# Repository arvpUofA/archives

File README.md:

# ARCHIVES

Last updated: 26th Aug 2016

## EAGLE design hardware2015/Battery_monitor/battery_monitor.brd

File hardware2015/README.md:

# Hardware for Aqua Ursa (2015)

* 2 x Battery Display (Battery_monitor/battery_display) [ Dim: 01.1 x 3.95 in ]
* 4 x Battery Monitor (Battery_monitor/battery_monitor) [ Dim: 0.73 x 1.59 in ]
* 2 x Display (Display/display) [ Dim: 2.72 x 3.79 in ]
* 2 x Motor (Motor/Motor_board) [ Dim: 4.65 x 3.66 in ]
* 2 x Sensor (Sensor/sensors) [ Dim: 1.51 x 1.25 in ]
* 2 x Sonar (Sonar/Sonar) [ Dim: 3.91 x 3.15 in ]

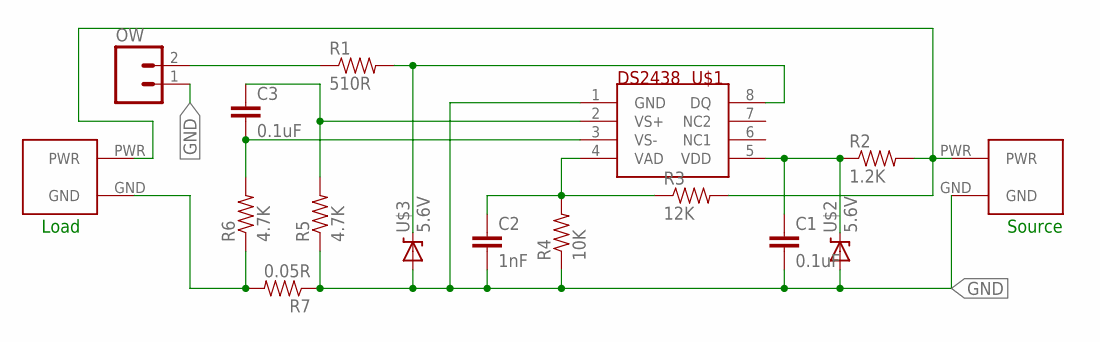
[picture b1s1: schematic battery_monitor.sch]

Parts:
C1, C3: 0.1uF; 0805
C2: 1nF; 0805
LOAD: AND_PWR
OW: M02POLAR_LOCK; MOLEX-1X2_LOCK
R1: 510R; 0805
R2: 1.2K; 0805
R3: 12K; 0805
R4: 10K; 0805
R5, R6: 4.7K; 0805
R7: 0.05R; 1206
SOURCE: AND_PWR
U$1: DS2438Z; SOIC8
U$2, U$3: 5.6V; SMB-DIODE

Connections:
GND: C1.2, C2.2, OW.1, R4.1, R5.1, R7.1, SOURCE.GND, U$1.1 (GND), U$2.A, U$3.A
unnamed: C1.1, R2.1, U$1.5 (VDD), U$2.C
unnamed: C3.2, R6.2, U$1.3 (VS-)
unnamed: C2.1, R3.1, R4.2, U$1.4 (VAD)
unnamed: OW.2, R1.1
unnamed: R1.2, U$1.8 (DQ), U$3.C
unnamed: LOAD.GND, R6.1, R7.2
unnamed: C3.1, R5.2, U$1.2 (VS+)
PWR: LOAD.PWR, R2.2, R3.2, SOURCE.PWR

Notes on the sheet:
Load
Source

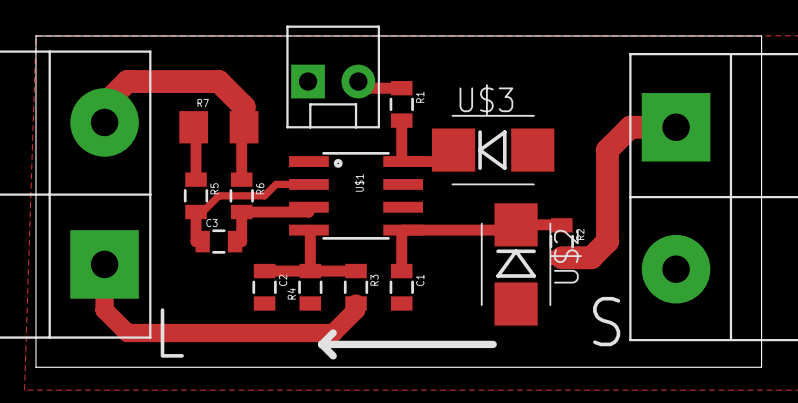
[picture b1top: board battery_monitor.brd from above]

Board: 2 copper layers, 40.3 x 18.4 mm, 16 parts (0 on the bottom side), 9 nets.

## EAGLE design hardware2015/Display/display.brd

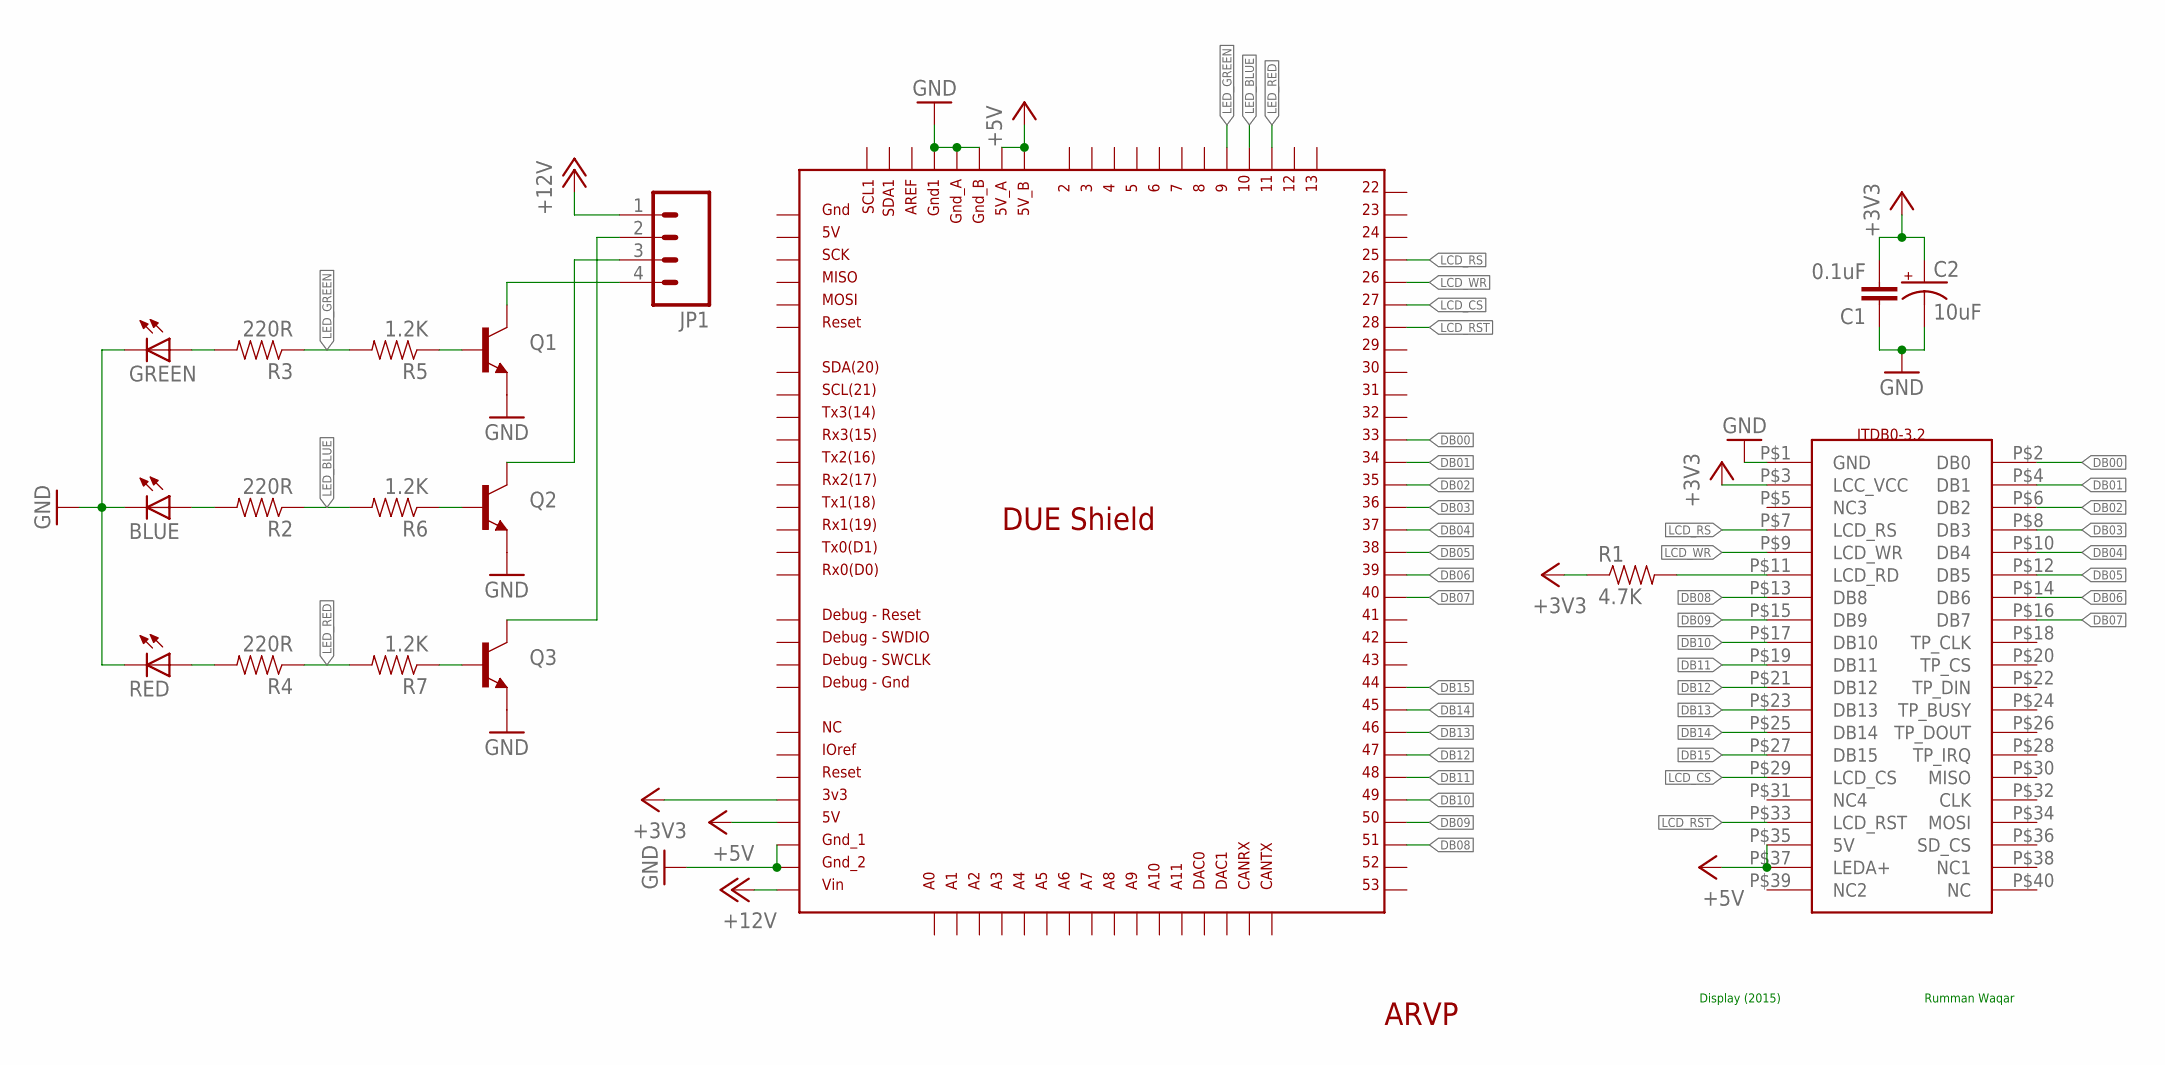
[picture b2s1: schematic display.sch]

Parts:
BLUE: LED1206; LED-1206
C1: 0.1uF; 1206
C2: 10uF; EIA3216
GREEN: LED1206; LED-1206
JP1: M04POLAR; MOLEX-1X4
Q1, Q2, Q3: TRANSISTOR_NPN"; SOT223
R1: 4.7K; 0805
R2, R3, R4: 220R; 1206
R5, R6, R7: 1.2K; 1206
RED: LED1206; LED-1206
U$1: DUE(NORMAL)
U$2: ARVP_LOGO; ARVP
U$3: ITDB0-3.2; ITDB02-3.2

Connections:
+3V3: C1.2, C2.A (+), R1.1, U$1.3V3, U$3.P$3 (LCC_VCC)
+5V: U$1.5V, U$1.5V_A, U$1.5V_B, U$3.P$35 (5V), U$3.P$37 (LEDA+)
+12V: JP1.1, U$1.VIN
DB00: U$1.33, U$3.P$2 (DB0)
DB01: U$1.34, U$3.P$4 (DB1)
DB02: U$1.35, U$3.P$6 (DB2)
DB03: U$1.36, U$3.P$8 (DB3)
DB04: U$1.37, U$3.P$10 (DB4)
DB05: U$1.38, U$3.P$12 (DB5)
DB06: U$1.39, U$3.P$14 (DB6)
DB07: U$1.40, U$3.P$16 (DB7)
DB08: U$1.51, U$3.P$13 (DB8)
DB09: U$1.50, U$3.P$15 (DB9)
DB10: U$1.49, U$3.P$17 (DB10)
DB11: U$1.48, U$3.P$19 (DB11)
DB12: U$1.47, U$3.P$21 (DB12)
DB13: U$1.46, U$3.P$23 (DB13)
DB14: U$1.45, U$3.P$25 (DB14)
DB15: U$1.44, U$3.P$27 (DB15)
GND: BLUE.C, C1.1, C2.C (-), GREEN.C, Q1.3 (E), Q2.3 (E), Q3.3 (E), RED.C, U$1.GND1, U$1.GND_1, U$1.GND_2, U$1.GND_A, U$1.GND_B, U$3.P$1 (GND)
LCD_CS: U$1.27, U$3.P$29 (LCD_CS)
LCD_RS: U$1.25, U$3.P$7 (LCD_RS)
LCD_RST: U$1.28, U$3.P$33 (LCD_RST)
LCD_WR: U$1.26, U$3.P$9 (LCD_WR)
LED_BLUE: R2.1, R6.2, U$1.10
LED_GREEN: R3.1, R5.2, U$1.9
LED_RED: R4.1, R7.2, U$1.11
unnamed: R1.2, U$3.P$11 (LCD_RD)
unnamed: JP1.4, Q1.2 (C)
unnamed: JP1.3, Q2.2 (C)
unnamed: Q3.1 (B), R7.1
unnamed: JP1.2, Q3.2 (C)
unnamed: Q2.1 (B), R6.1
unnamed: Q1.1 (B), R5.1
unnamed: GREEN.A, R3.2
unnamed: R4.2, RED.A
unnamed: BLUE.A, R2.2

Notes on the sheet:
Display (2015)
Rumman Waqar

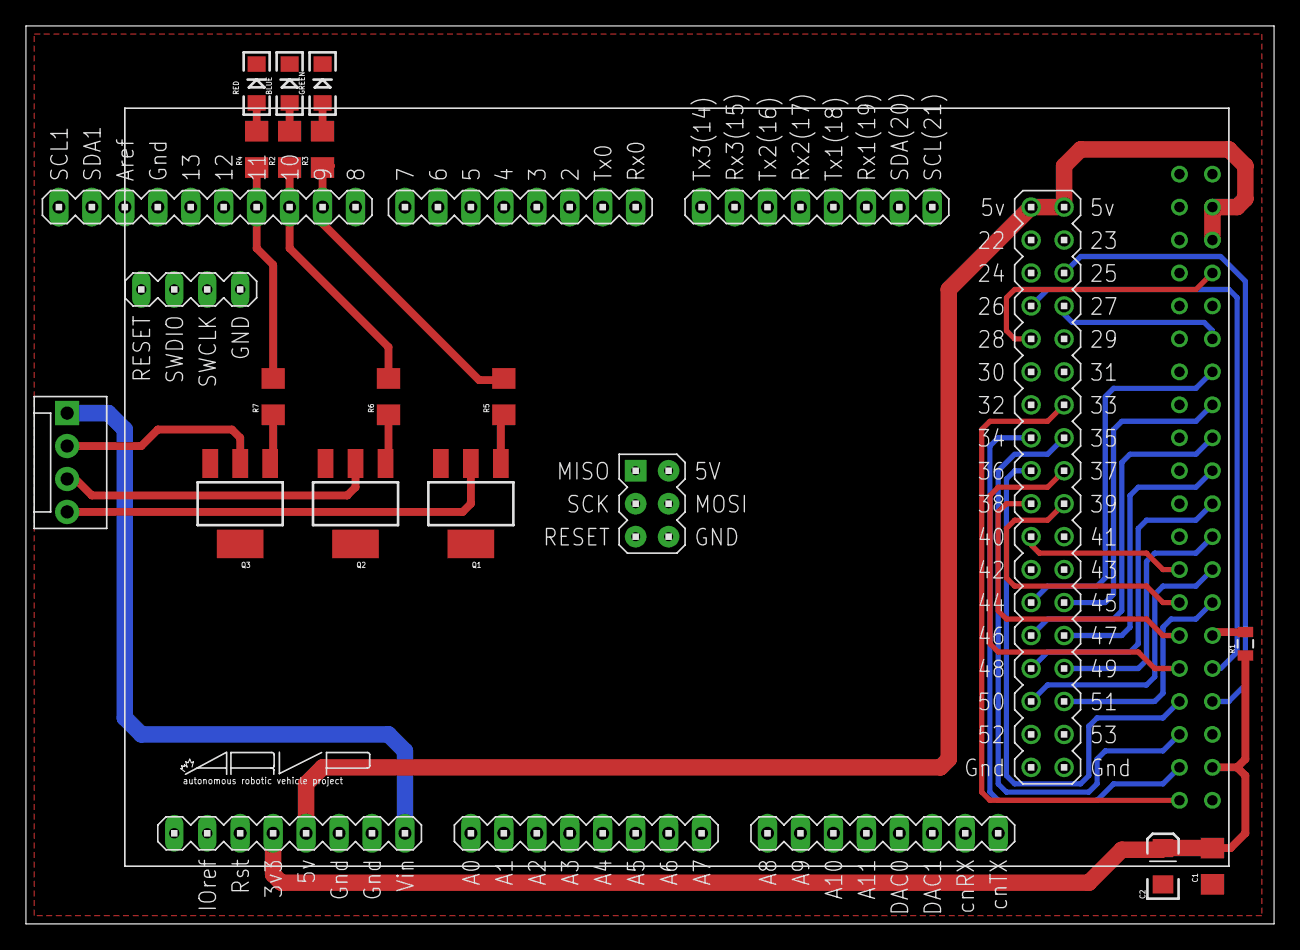
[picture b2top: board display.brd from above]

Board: 2 copper layers, 96.2 x 69.2 mm, 19 parts (0 on the bottom side), 37 nets.

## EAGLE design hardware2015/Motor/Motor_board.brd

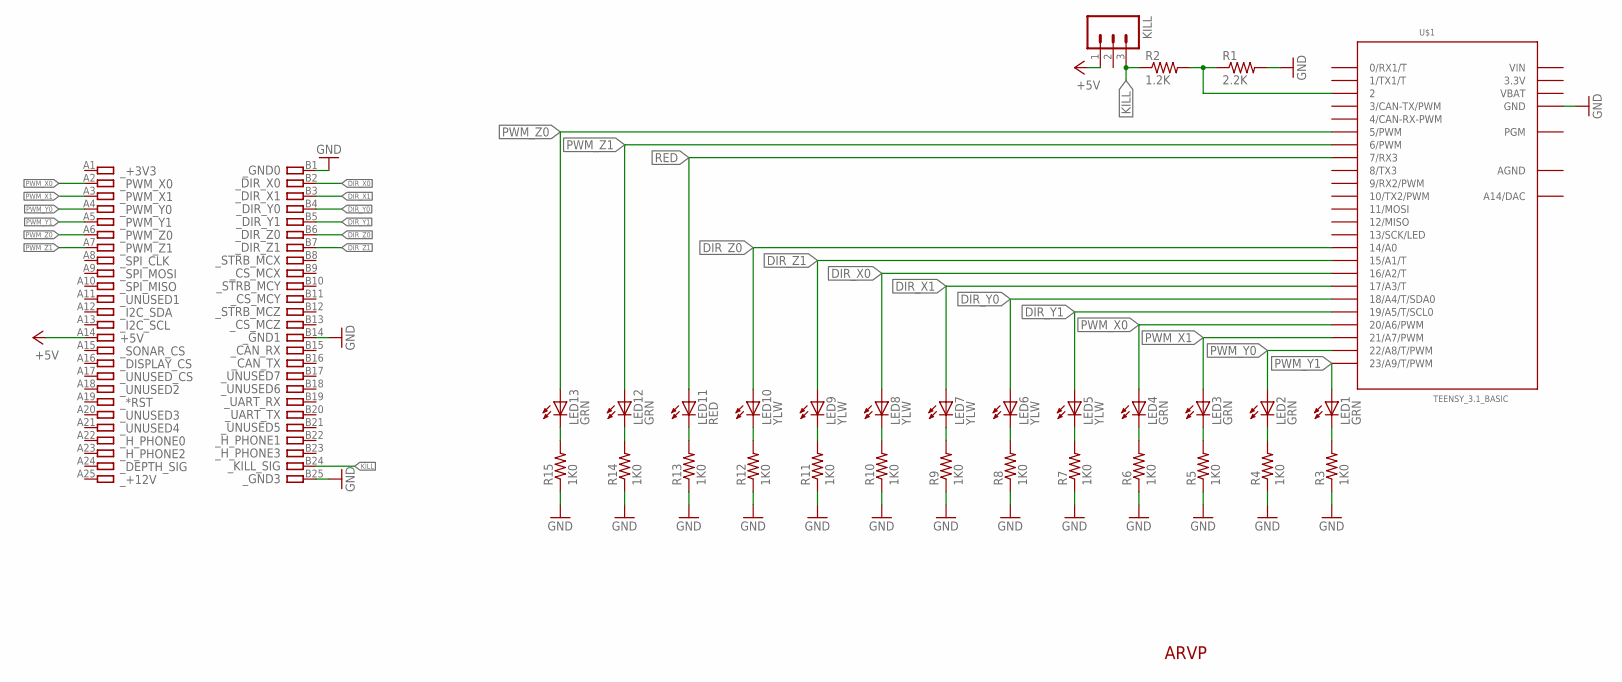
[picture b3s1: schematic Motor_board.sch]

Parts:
KILL: M03LONGPADS; 1X03_LONGPADS
LED1, LED2, LED3, LED4, LED12, LED13: GRN; LED-1206
LED5, LED6, LED7, LED8, LED9, LED10: YLW; LED-1206
LED11: RED; LED-1206
R1: 2.2K; 1206
R2: 1.2K; 1206
R3, R4, R5, R6, R7, R8, R9, R10, R11, R12, R13, R14, R15: 1K0; 1206
U$1: TEENSY_3.1_BASIC
U$4: ARVP_LOGO; ARVP
U$19: CARD_50PIN

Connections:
3.3V: U$1.3.3V, U$1.3.3V1 (3.3V)
+5V: KILL.1, U$19.A14
AGND: U$1.AGND
DIR_X0: LED8.A, U$1.16/A2 (16/A2/T), U$19.B2
DIR_X1: LED7.A, U$1.17/A3 (17/A3/T), U$19.B3
DIR_Y0: LED6.A, U$1.18/A4 (18/A4/T/SDA0), U$19.B4
DIR_Y1: LED5.A, U$1.19/A5 (19/A5/T/SCL0), U$19.B5
DIR_Z0: LED10.A, U$1.14/A0, U$19.B6
DIR_Z1: LED9.A, U$1.15/A1 (15/A1/T), U$19.B7
GND: R1.2, R3.1, R4.1, R5.1, R6.1, R7.1, R8.1, R9.1, R10.1, R11.1, R12.1, R13.1, R14.1, R15.1, U$1.GND, U$1.GND1 (GND), U$19.B1, U$19.B14, U$19.B25
KILL: KILL.3, R2.1, U$19.B24
unnamed: LED1.C, R3.2
unnamed: LED2.C, R4.2
unnamed: LED3.C, R5.2
unnamed: LED4.C, R6.2
unnamed: LED5.C, R7.2
unnamed: LED6.C, R8.2
unnamed: LED7.C, R9.2
unnamed: LED8.C, R10.2
unnamed: R1.1, R2.2, U$1.2
unnamed: LED12.C, R14.2
unnamed: LED11.C, R13.2
unnamed: LED9.C, R11.2
unnamed: LED10.C, R12.2
unnamed: LED13.C, R15.2
PWM_X0: LED4.A, U$1.20/A6 (20/A6/PWM), U$19.A2
PWM_X1: LED3.A, U$1.21/A7 (21/A7/PWM), U$19.A3
PWM_Y0: LED2.A, U$1.22/A8 (22/A8/T/PWM), U$19.A4
PWM_Y1: LED1.A, U$1.23/A9 (23/A9/T/PWM), U$19.A5
PWM_Z0: LED13.A, U$1.5 (5/PWM), U$19.A6
PWM_Z1: LED12.A, U$1.6 (6/PWM), U$19.A7
RED: LED11.A, U$1.7 (7/RX3)
VBAT: U$1.VBAT
VIN: U$1.VIN

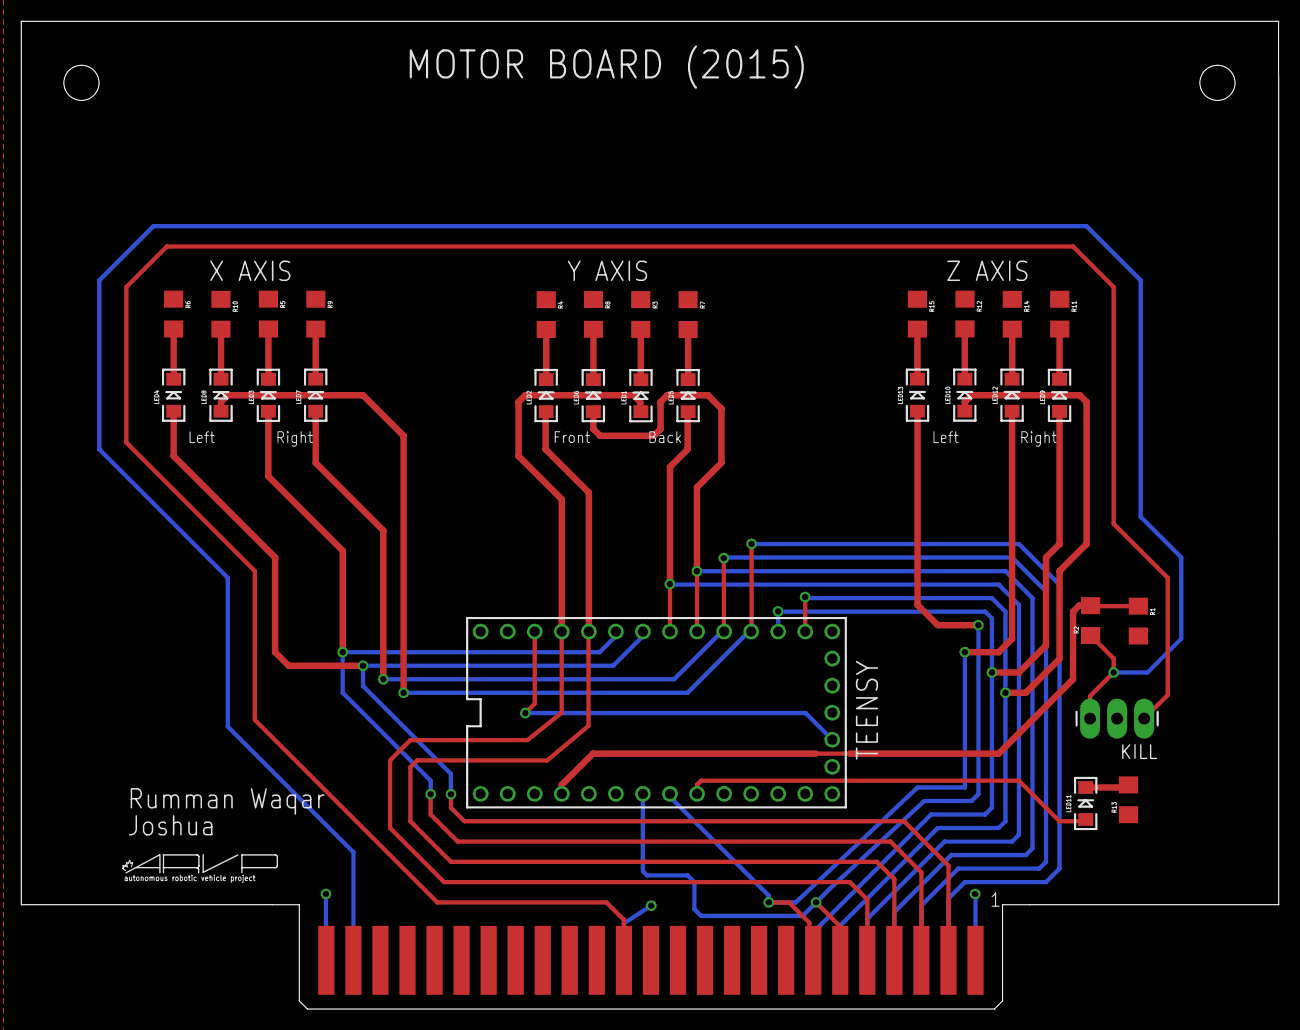
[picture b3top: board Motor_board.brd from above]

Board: 2 copper layers, 118.1 x 92.8 mm, 34 parts (0 on the bottom side), 31 nets.

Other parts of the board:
JP2, JP3: STAND-OFF

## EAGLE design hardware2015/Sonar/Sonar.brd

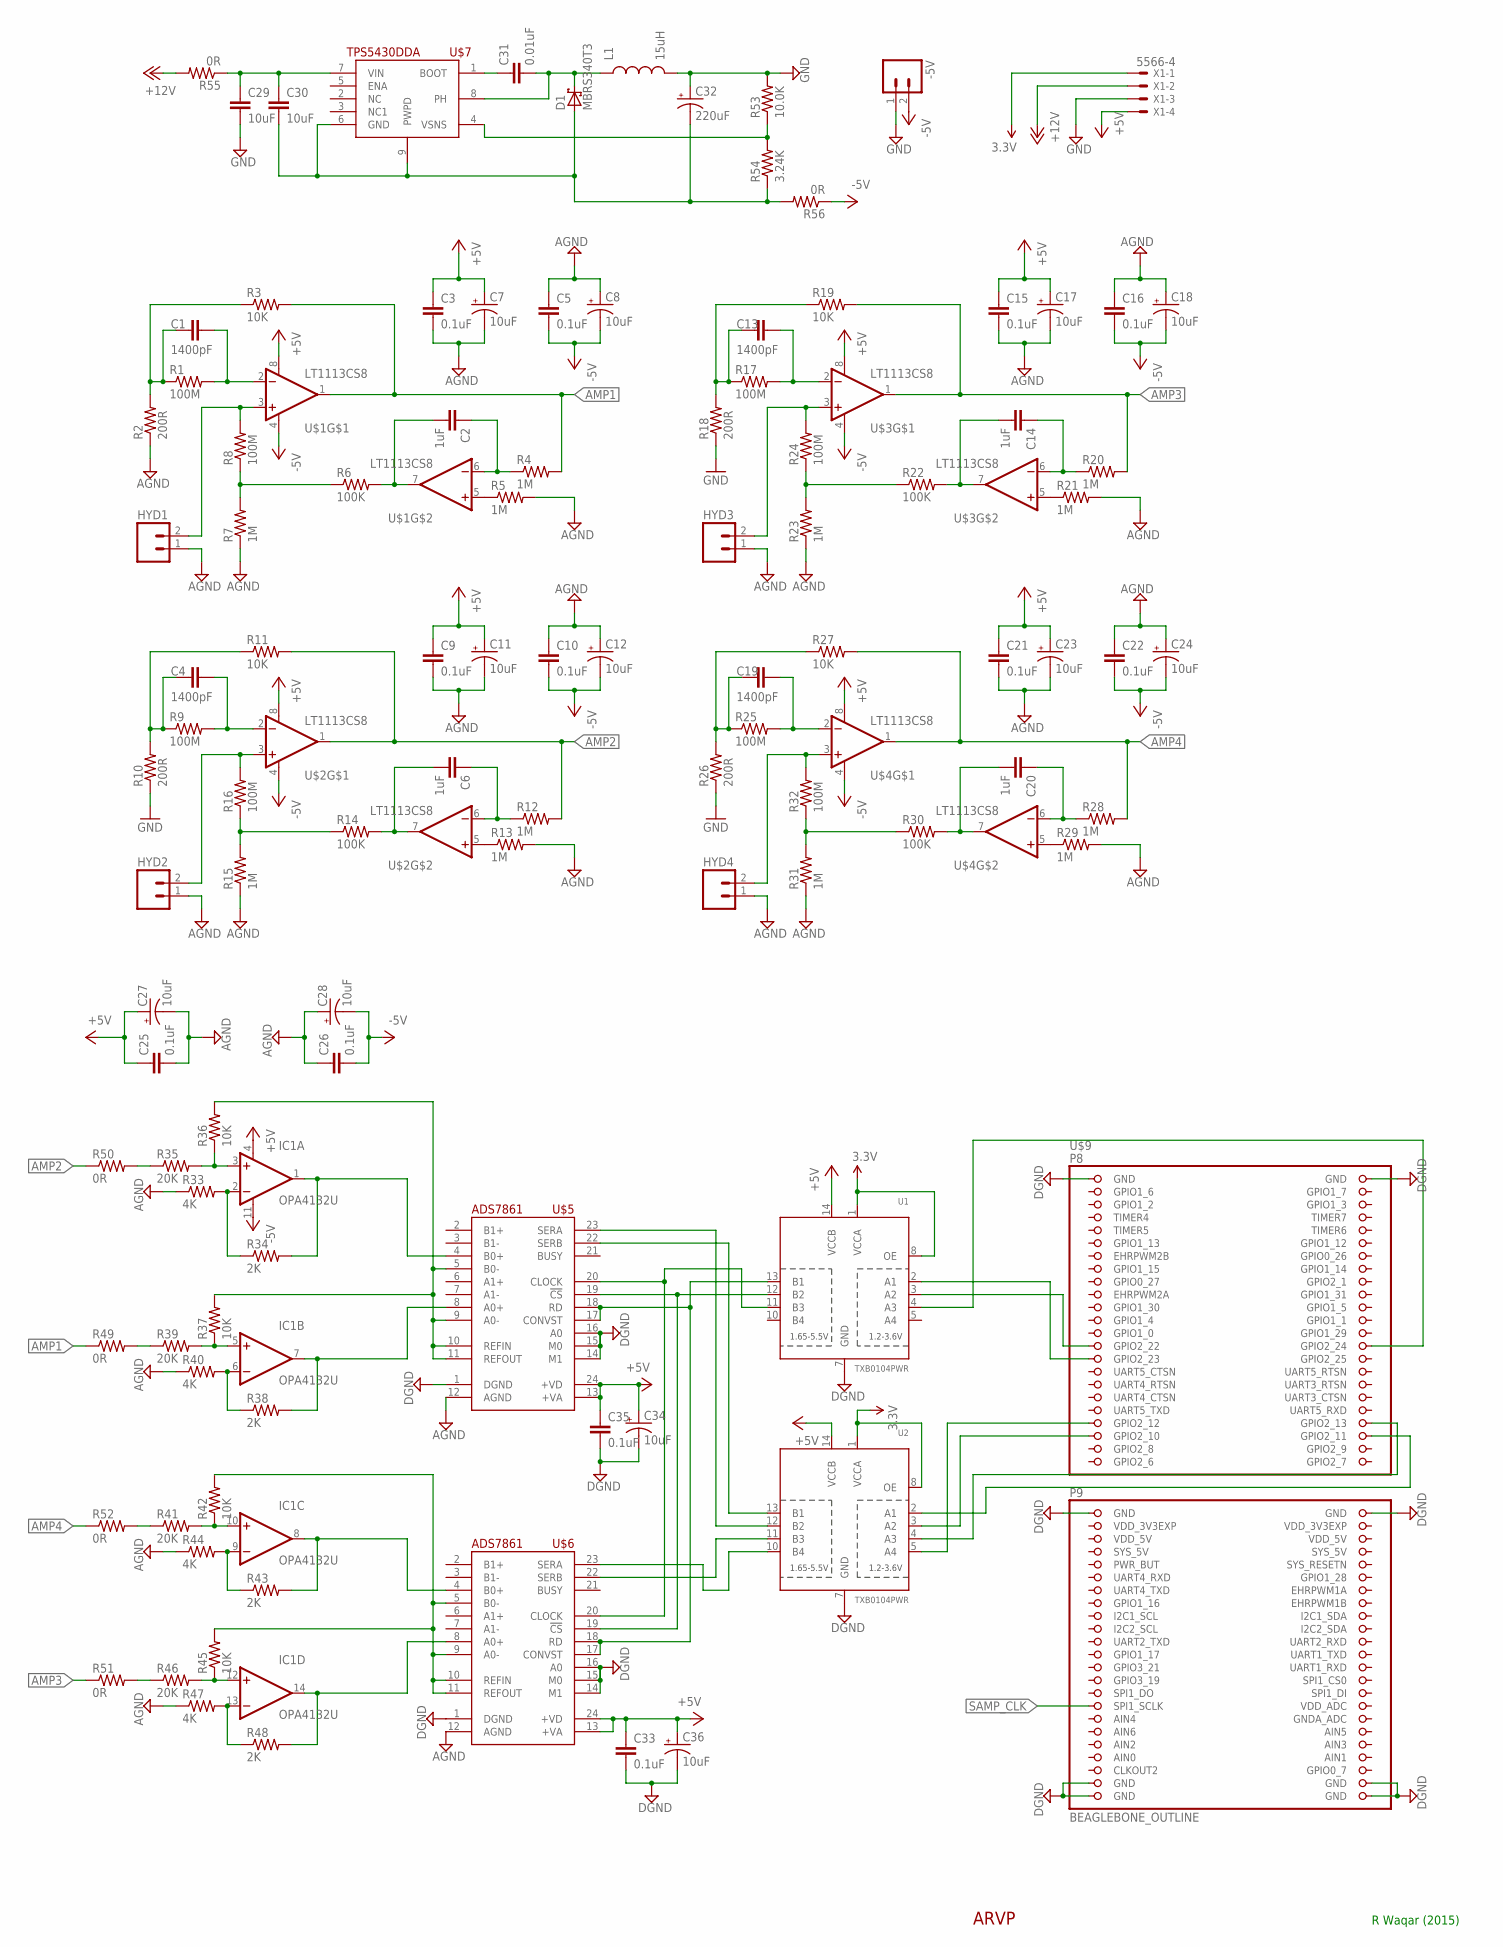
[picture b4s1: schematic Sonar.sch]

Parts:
-5V: M02PTH3; 1X02_LONGPADS
C1, C4, C13, C19: 1400pF; 0805
C2, C6, C14, C20: 1uF; 0805
C3, C5, C9, C10, C15, C16, C21, C22, C25, C26, C33, C35: 0.1uF; 0805
C7, C8, C11, C12, C17, C18, C23, C24, C27, C28, C34, C36: 10uF; EIA3216
C29, C30: 10uF; 0805
C31: 0.01uF; 0805
C32: 220uF; EIA7343
D1: MBRS340T3; SMC
HYD1, HYD2, HYD3, HYD4: M02POLAR; MOLEX-1X2
IC1: OPA4132U; SO14
L1: 15uH; 1210
R1, R8, R9, R16, R17, R24, R25, R32: 100M; 0805
R2, R10, R18, R26: 200R; AXIAL-0.3
R3, R11, R19, R27: 10K; AXIAL-0.3
R4, R5, R7, R12, R13, R15, R20, R21, R23, R28, R29, R31: 1M; 0805
R6, R14, R22, R30: 100K; 0805
R33, R40, R44, R47: 4K; 0805
R34, R38, R43, R48: 2K; 0805
R35, R39, R41, R46: 20K; 0805
R36, R37, R42, R45: 10K; 0805
R49, R50, R51, R52, R55, R56: 0R; 1206
R53: 10.0K; 0805
R54: 3.24K; 0805
U1, U2: TXB0104PWR; TSSOP14
U$1, U$2, U$3, U$4: LT1113CS8; SO-08
U$5, U$6: ADS7861E; SSOP24
U$7: TPS5430DDA; SOIC8-POWERPAD
U$8: ARVP_LOGO; ARVP
U$9: BEAGLEBONE_OUTLINE; BEAGLEBONE_SHIELD
X1: 5566-4

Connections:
3.3V: U1.1 (VCCA), U1.8 (OE), U2.1 (VCCA), U2.8 (OE), X1.1
+5V: C3.1, C7.A (+), C9.1, C11.A (+), C15.1, C17.A (+), C21.1, C23.A (+), C25.1, C27.A (+), C33.1, C34.A (+), C35.1, C36.A (+), IC1.4 (V+), U1.14 (VCCB), U2.14 (VCCB), U$1.8 (V+), U$2.8 (V+), U$3.8 (V+), U$4.8 (V+), U$5.13 (+VA), U$5.24 (+VD), U$6.13 (+VA), U$6.24 (+VD), X1.4
+12V: R55.2, X1.2
-5V: -5V.2, C5.2, C8.C (-), C10.2, C12.C (-), C16.2, C18.C (-), C22.2, C24.C (-), C26.2, C28.C (-), IC1.11 (V-), R56.1, U$1.4 (V-), U$2.4 (V-), U$3.4 (V-), U$4.4 (V-)
AIN0: U$9.85 (AIN0)
AMP1: R3.P$2 (2), R4.2, R49.1, U$1.1 (OUT)
AMP2: R11.P$2 (2), R12.2, R50.1, U$2.1 (OUT)
AMP3: R19.P$2 (2), R20.2, R51.1, U$3.1 (OUT)
AMP4: R27.P$2 (2), R28.2, R52.1, U$4.1 (OUT)
GND: -5V.1, C3.2, C5.1, C7.C (-), C8.A (+), C9.2, C10.1, C11.C (-), C12.A (+), C15.2, C16.1, C17.C (-), C18.A (+), C21.2, C22.1, C23.C (-), C24.A (+), C25.2, C26.1, C27.C (-), C28.A (+), C29.2, C32.A (+), C33.2, C34.C (-), C35.2, C36.C (-), HYD1.1, HYD2.1, HYD3.1, HYD4.1, L1.2, R2.P$1 (1), R5.2, R7.1, R10.P$1 (1), R13.2, R15.1, R18.P$1 (1), R21.2, R23.1, R26.P$1 (1), R29.2, R31.1, R33.1, R40.1, R44.1, R47.1, R53.2, U1.7 (GND), U2.7 (GND), U$5.1 (DGND), U$5.12 (AGND), U$5.14 (M1), U$5.15 (M0), U$5.16 (A0), U$6.1 (DGND), U$6.12 (AGND), U$6.14 (M1), U$6.15 (M0), U$6.16 (A0), U$9.1 (GND), U$9.2 (GND), U$9.47 (GND), U$9.48 (GND), U$9.89 (GND), U$9.90 (GND), U$9.91 (GND), U$9.92 (GND), X1.3
unnamed: C1.2, R1.1, R2.P$2 (2), R3.P$1 (1)
unnamed: C1.1, R1.2, U$1.2 (-IN)
unnamed: C4.2, R9.1, R10.P$2 (2), R11.P$1 (1)
unnamed: R6.1, R7.2, R8.1
unnamed: HYD1.2, R8.2, U$1.3 (+IN)
unnamed: C4.1, R9.2, U$2.2 (-IN)
unnamed: C2.2, R6.2, U$1.7 (OUT)
unnamed: R5.1, U$1.5 (+IN)
unnamed: C2.1, R4.1, U$1.6 (-IN)
unnamed: R14.1, R15.2, R16.1
unnamed: HYD2.2, R16.2, U$2.3 (+IN)
unnamed: C6.2, R14.2, U$2.7 (OUT)
unnamed: R13.1, U$2.5 (+IN)
unnamed: C6.1, R12.1, U$2.6 (-IN)
unnamed: C13.2, R17.1, R18.P$2 (2), R19.P$1 (1)
unnamed: C13.1, R17.2, U$3.2 (-IN)
unnamed: R22.1, R23.2, R24.1
unnamed: HYD3.2, R24.2, U$3.3 (+IN)
unnamed: C14.2, R22.2, U$3.7 (OUT)
unnamed: R21.1, U$3.5 (+IN)
unnamed: C14.1, R20.1, U$3.6 (-IN)
unnamed: C19.2, R25.1, R26.P$2 (2), R27.P$1 (1)
unnamed: C19.1, R25.2, U$4.2 (-IN)
unnamed: R30.1, R31.2, R32.1
unnamed: HYD4.2, R32.2, U$4.3 (+IN)
unnamed: C20.2, R30.2, U$4.7 (OUT)
unnamed: R29.1, U$4.5 (+IN)
unnamed: C20.1, R28.1, U$4.6 (-IN)
unnamed: IC1.3 (+IN), R35.2, R36.1
unnamed: IC1.1 (OUT), R34.2, U$5.4 (B0+)
unnamed: IC1.2 (-IN), R33.2, R34.1
unnamed: R36.2, R37.2, U$5.5 (B0-), U$5.9 (A0-), U$5.10 (REFIN), U$5.11 (REFOUT)
unnamed: IC1.5 (+IN), R37.1, R39.2
unnamed: IC1.6 (-IN), R38.1, R40.2
unnamed: IC1.7 (OUT), R38.2, U$5.8 (A0+)
unnamed: IC1.13 (-IN), R47.2, R48.1
unnamed: IC1.14 (OUT), R48.2, U$6.8 (A0+)
unnamed: IC1.9 (-IN), R43.1, R44.2
unnamed: IC1.8 (OUT), R43.2, U$6.4 (B0+)
unnamed: IC1.10 (+IN), R41.2, R42.1
unnamed: IC1.12 (+IN), R45.1, R46.2
unnamed: R42.2, R45.2, U$6.5 (B0-), U$6.9 (A0-), U$6.10 (REFIN), U$6.11 (REFOUT)
unnamed: R41.1, R52.2
unnamed: R46.1, R51.2
unnamed: R35.1, R50.2
unnamed: R39.1, R49.2
unnamed: U1.4 (A3), U$9.28 (GPIO2_24)
unnamed: U1.13 (B1), U$5.17 (CONVST), U$5.18 (RD), U$6.17 (CONVST), U$6.18 (RD)
unnamed: U1.11 (B3), U$5.20 (CLOCK), U$6.20 (CLOCK)
unnamed: U1.12 (B2), U$5.19 (!CS!), U$6.19 (!CS!)
unnamed: U2.10 (B4), U$6.23 (SERA)
unnamed: U2.13 (B1), U$5.22 (SERB)
unnamed: U2.11 (B3), U$6.22 (SERB)
unnamed: U2.5 (A4), U$9.39 (GPIO2_12)
unnamed: U2.12 (B2), U$5.23 (SERA)
unnamed: U2.3 (A2), U$9.41 (GPIO2_10)
unnamed: U2.2 (A1), U$9.42 (GPIO2_11)
unnamed: U2.4 (A3), U$9.40 (GPIO2_13)
unnamed: U1.2 (A1), U$9.29 (GPIO2_23)
unnamed: C29.1, C30.1, R55.1, U$7.7 (VIN)
unnamed: U1.3 (A2), U$9.27 (GPIO2_22)
unnamed: C31.1, U$7.1 (BOOT)
unnamed: C31.2, D1.C, L1.1, U$7.8 (PH)
unnamed: R53.1, R54.2, U$7.4 (VSNS)
unnamed: C30.2, C32.C (-), D1.A, R54.1, R56.2, U$7.6 (GND), U$7.9 (PWPD)
SAMP_CLK: U$9.77 (SPI1_SCLK)
SYS_5V: U$9.53 (SYS_5V)
VDD_3V3EXP: U$9.49 (VDD_3V3EXP), U$9.50 (VDD_3V3EXP)
VDD_5V: U$9.51 (VDD_5V), U$9.52 (VDD_5V)

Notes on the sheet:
R Waqar (2015)

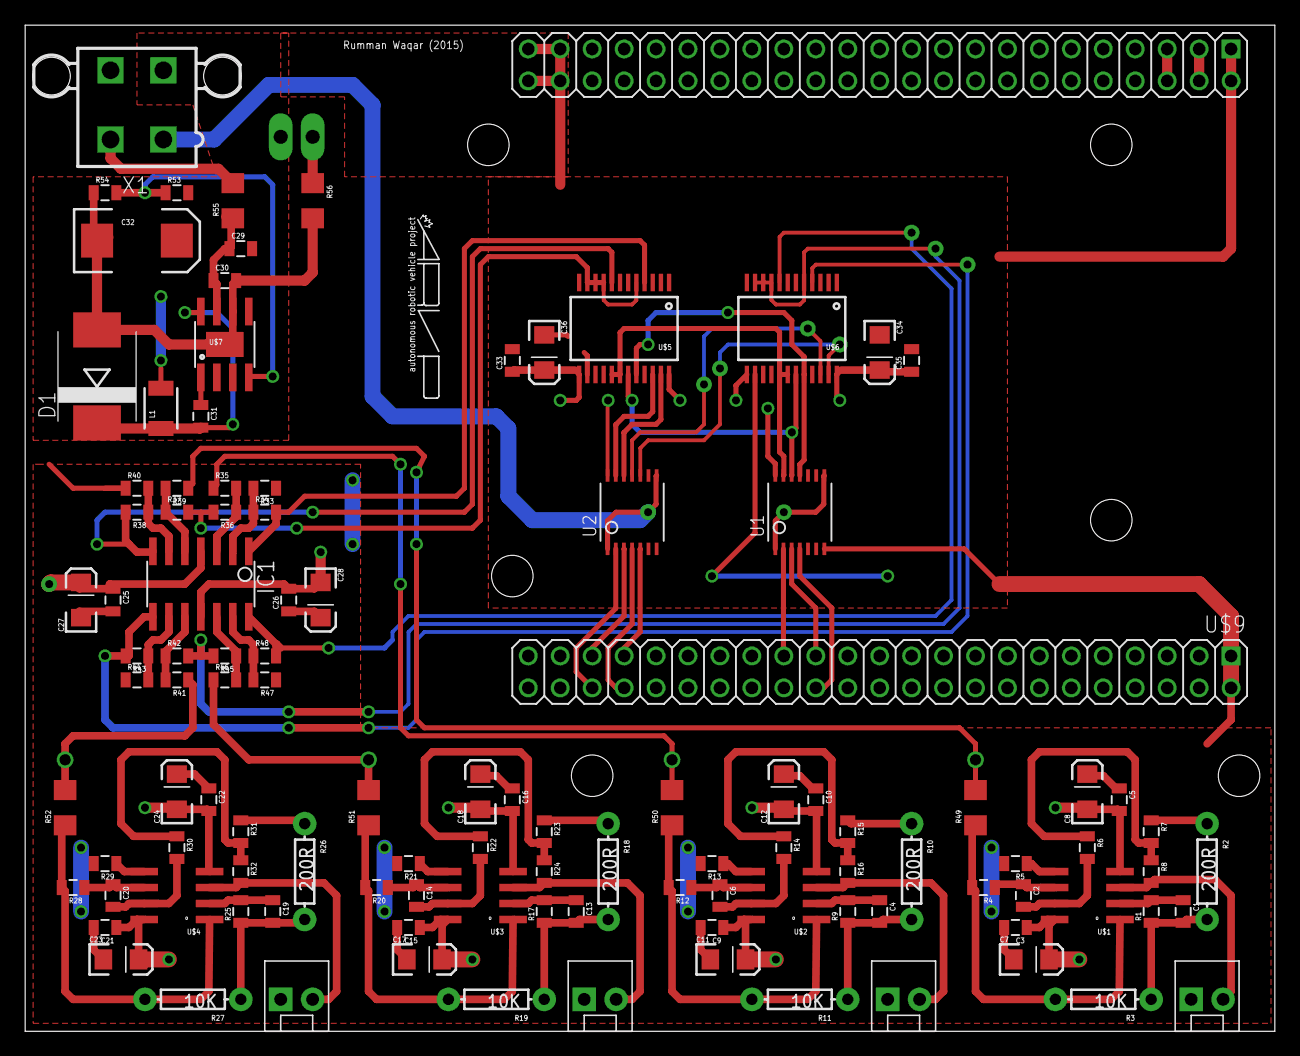
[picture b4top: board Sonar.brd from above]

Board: 2 copper layers, 99.4 x 80.0 mm, 118 parts (0 on the bottom side), 76 nets.

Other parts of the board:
U$10, U$11, U$12, U$13, U$14, U$15: STAND-OFF

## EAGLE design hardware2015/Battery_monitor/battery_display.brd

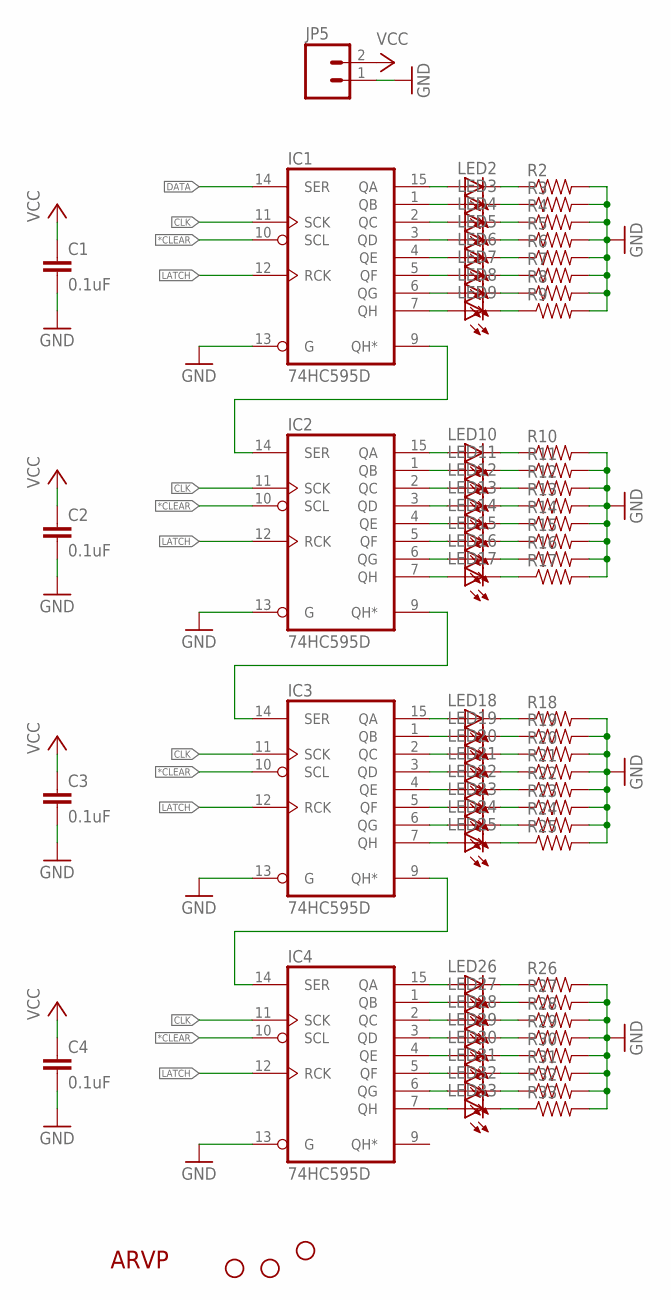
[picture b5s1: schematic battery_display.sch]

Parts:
C1, C2, C3, C4: 0.1uF; 1206
IC1, IC2, IC3, IC4: 74HC595D; SO16
JP2, JP3, JP4: STAND-OFF
JP5: M02POLAR_LOCK; MOLEX-1X2_LOCK
LED2, LED3, LED4, LED5, LED6, LED7, LED8, LED9, LED10, LED11, LED12, LED13, LED14, LED15, LED16, LED17, LED18, LED19, LED20, LED21, LED22, LED23, LED24, LED25, LED26, LED27, LED28, LED29, LED30, LED31, LED32, LED33: LED1206; LED-1206
R2, R3, R4, R5, R6, R7, R8, R9, R10, R11, R12, R13, R14, R15, R16, R17, R18, R19, R20, R21, R22, R23, R24, R25, R26, R27, R28, R29, R30, R31, R32, R33: RESISTOR1206; 1206
U$2: ARVP_LOGO; ARVP

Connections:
*CLEAR: IC1.10 (SCL), IC2.10 (SCL), IC3.10 (SCL), IC4.10 (SCL)
CLK: IC1.11 (SCK), IC2.11 (SCK), IC3.11 (SCK), IC4.11 (SCK)
DATA: IC1.14 (SER)
GND: C1.2, C2.2, C3.2, C4.2, IC1.8 (GND), IC1.13 (G), IC2.8 (GND), IC2.13 (G), IC3.8 (GND), IC3.13 (G), IC4.8 (GND), IC4.13 (G), JP5.1, R2.2, R3.2, R4.2, R5.2, R6.2, R7.2, R8.2, R9.2, R10.2, R11.2, R12.2, R13.2, R14.2, R15.2, R16.2, R17.2, R18.2, R19.2, R20.2, R21.2, R22.2, R23.2, R24.2, R25.2, R26.2, R27.2, R28.2, R29.2, R30.2, R31.2, R32.2, R33.2
LATCH: IC1.12 (RCK), IC2.12 (RCK), IC3.12 (RCK), IC4.12 (RCK)
unnamed: LED2.C, R2.1
unnamed: LED3.C, R3.1
unnamed: LED4.C, R4.1
unnamed: LED5.C, R5.1
unnamed: LED6.C, R6.1
unnamed: LED7.C, R7.1
unnamed: LED8.C, R8.1
unnamed: LED9.C, R9.1
unnamed: LED10.C, R10.1
unnamed: LED11.C, R11.1
unnamed: LED12.C, R12.1
unnamed: LED13.C, R13.1
unnamed: LED14.C, R14.1
unnamed: LED15.C, R15.1
unnamed: LED16.C, R16.1
unnamed: LED17.C, R17.1
unnamed: LED18.C, R18.1
unnamed: LED19.C, R19.1
unnamed: LED20.C, R20.1
unnamed: LED21.C, R21.1
unnamed: LED22.C, R22.1
unnamed: LED23.C, R23.1
unnamed: LED24.C, R24.1
unnamed: LED25.C, R25.1
unnamed: LED26.C, R26.1
unnamed: LED27.C, R27.1
unnamed: LED28.C, R28.1
unnamed: LED29.C, R29.1
unnamed: LED30.C, R30.1
unnamed: LED31.C, R31.1
unnamed: LED32.C, R32.1
unnamed: LED33.C, R33.1
unnamed: IC1.7 (QH), LED9.A
unnamed: IC1.6 (QG), LED8.A
unnamed: IC1.5 (QF), LED7.A
unnamed: IC1.4 (QE), LED6.A
unnamed: IC1.3 (QD), LED5.A
unnamed: IC1.2 (QC), LED4.A
unnamed: IC1.1 (QB), LED3.A
unnamed: IC1.15 (QA), LED2.A
unnamed: IC3.9 (QH*), IC4.14 (SER)
unnamed: IC2.9 (QH*), IC3.14 (SER)
unnamed: IC1.9 (QH*), IC2.14 (SER)
unnamed: IC2.15 (QA), LED10.A
unnamed: IC2.2 (QC), LED12.A
unnamed: IC2.1 (QB), LED11.A
unnamed: IC2.3 (QD), LED13.A
unnamed: IC2.4 (QE), LED14.A
unnamed: IC2.5 (QF), LED15.A
unnamed: IC2.6 (QG), LED16.A
unnamed: IC2.7 (QH), LED17.A
unnamed: IC3.15 (QA), LED18.A
unnamed: IC3.1 (QB), LED19.A
unnamed: IC3.2 (QC), LED20.A
unnamed: IC3.3 (QD), LED21.A
unnamed: IC3.4 (QE), LED22.A
unnamed: IC3.5 (QF), LED23.A
unnamed: IC3.6 (QG), LED24.A
unnamed: IC3.7 (QH), LED25.A
unnamed: IC4.15 (QA), LED26.A
unnamed: IC4.1 (QB), LED27.A
unnamed: IC4.2 (QC), LED28.A
unnamed: IC4.3 (QD), LED29.A
unnamed: IC4.4 (QE), LED30.A
unnamed: IC4.5 (QF), LED31.A
unnamed: IC4.6 (QG), LED32.A
unnamed: IC4.7 (QH), LED33.A
VCC: C1.1, C2.1, C3.1, C4.1, IC1.16 (VCC), IC2.16 (VCC), IC3.16 (VCC), IC4.16 (VCC), JP5.2

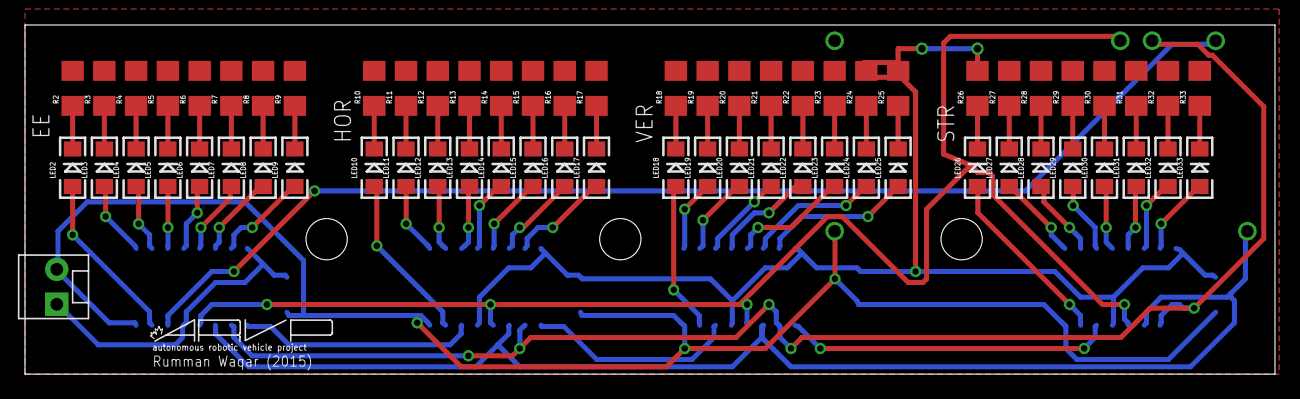
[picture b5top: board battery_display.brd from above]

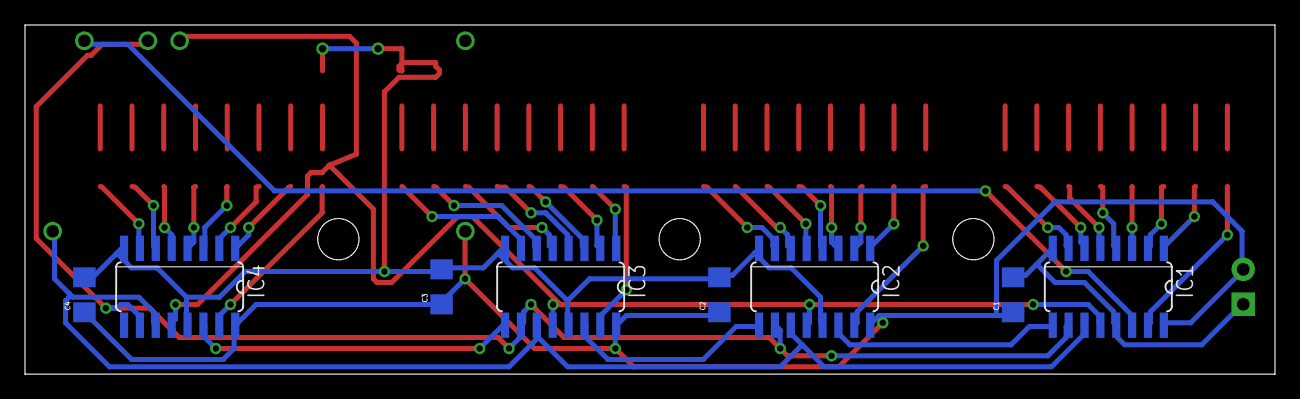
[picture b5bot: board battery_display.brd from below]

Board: 2 copper layers, 100.0 x 27.9 mm, 77 parts (8 on the bottom side), 72 nets.

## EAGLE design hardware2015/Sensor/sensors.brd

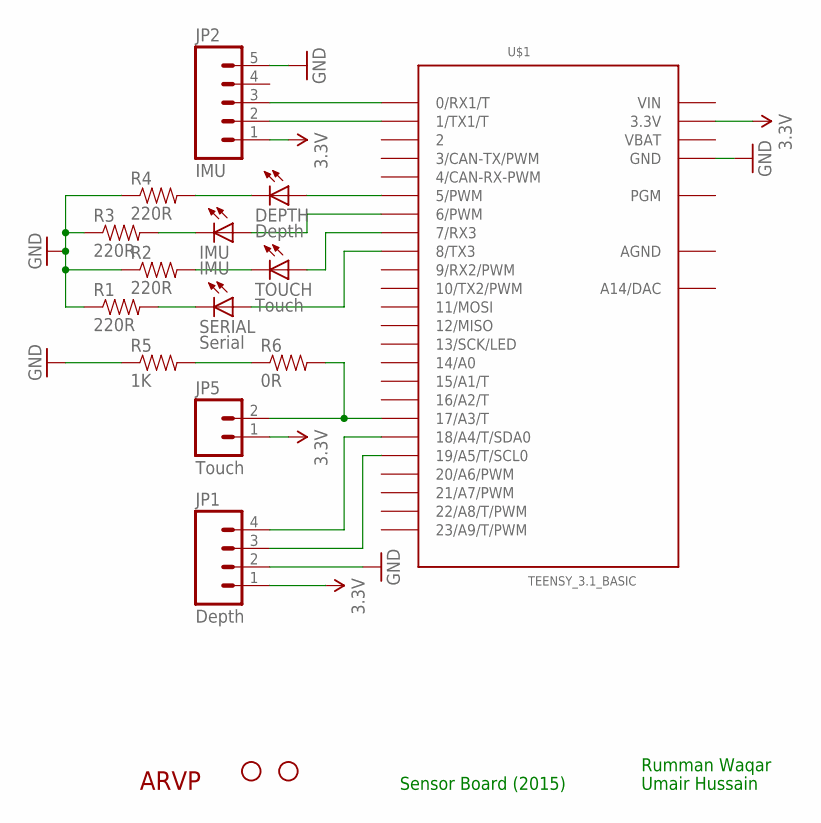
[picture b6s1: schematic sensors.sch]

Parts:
DEPTH: Depth; LED-1206
IMU: IMU; LED-1206
JP1: Depth; 1X04_LONGPADS
JP2: IMU; 1X05_LONGPADS
JP3, JP4: STAND-OFF
JP5: Touch; MOLEX-1X2
R1, R2, R3, R4: 220R; 1206
R5: 1K; 1206
R6: 0R; 1206
SERIAL: Serial; LED-1206
TOUCH: Touch; LED-1206
U$1: TEENSY_3.1_BASIC
U$2: ARVP_LOGO; ARVP

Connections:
3.3V: JP1.1, JP2.1, JP5.1, U$1.3.3V, U$1.3.3V1 (3.3V)
AGND: U$1.AGND
GND: JP1.2, JP2.5, R1.1, R2.1, R3.1, R4.1, R5.1, U$1.GND, U$1.GND1 (GND)
unnamed: DEPTH.A, U$1.5 (5/PWM)
unnamed: DEPTH.C, R4.2
unnamed: IMU.C, R3.2
unnamed: R2.2, TOUCH.C
unnamed: R1.2, SERIAL.C
unnamed: IMU.A, U$1.6 (6/PWM)
unnamed: TOUCH.A, U$1.7 (7/RX3)
unnamed: SERIAL.A, U$1.8 (8/TX3)
unnamed: JP2.2, U$1.1 (1/TX1/T)
unnamed: JP2.3, U$1.0 (0/RX1/T)
unnamed: JP5.2, R6.2, U$1.17/A3 (17/A3/T)
unnamed: R5.2, R6.1
unnamed: JP1.3, U$1.19/A5 (19/A5/T/SCL0)
unnamed: JP1.4, U$1.18/A4 (18/A4/T/SDA0)
VBAT: U$1.VBAT
VIN: U$1.VIN

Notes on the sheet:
Rumman Waqar
Umair Hussain
Sensor Board (2015)

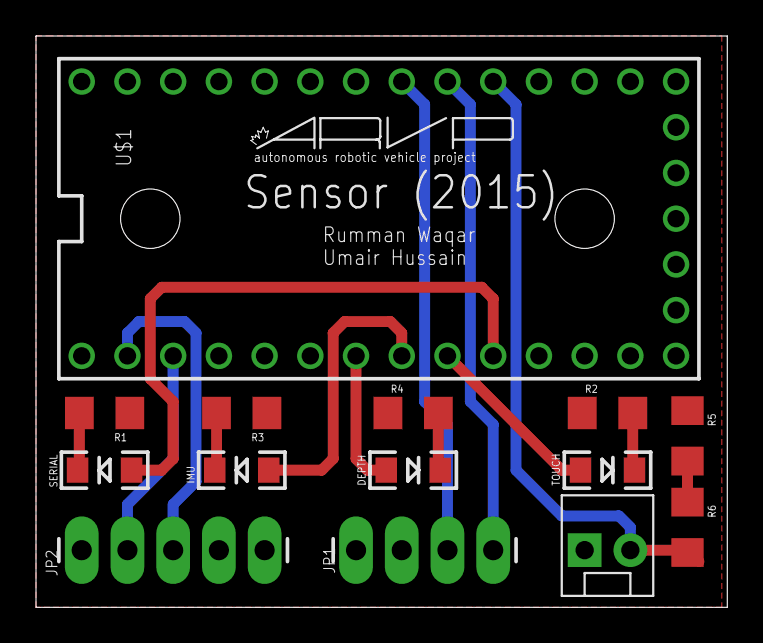
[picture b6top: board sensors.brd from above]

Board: 2 copper layers, 38.4 x 31.7 mm, 17 parts (0 on the bottom side), 16 nets.

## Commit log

2016-08-27 Added vision_temp
2016-08-27 Added vision repo (pre ros) made by veselin
2016-08-27 Added ros_lib
2016-08-27 Sonar code with pru and bbb
2016-08-27 Old diagnostics node
2016-08-27 Sensor (embedded)
2016-08-27 Added hardware 2014-2015 folder

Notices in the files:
parts and their libraries:
SparkFun: Licensing: CC v3.0 Share-Alike You are welcome to use this library for commercial purposes.
